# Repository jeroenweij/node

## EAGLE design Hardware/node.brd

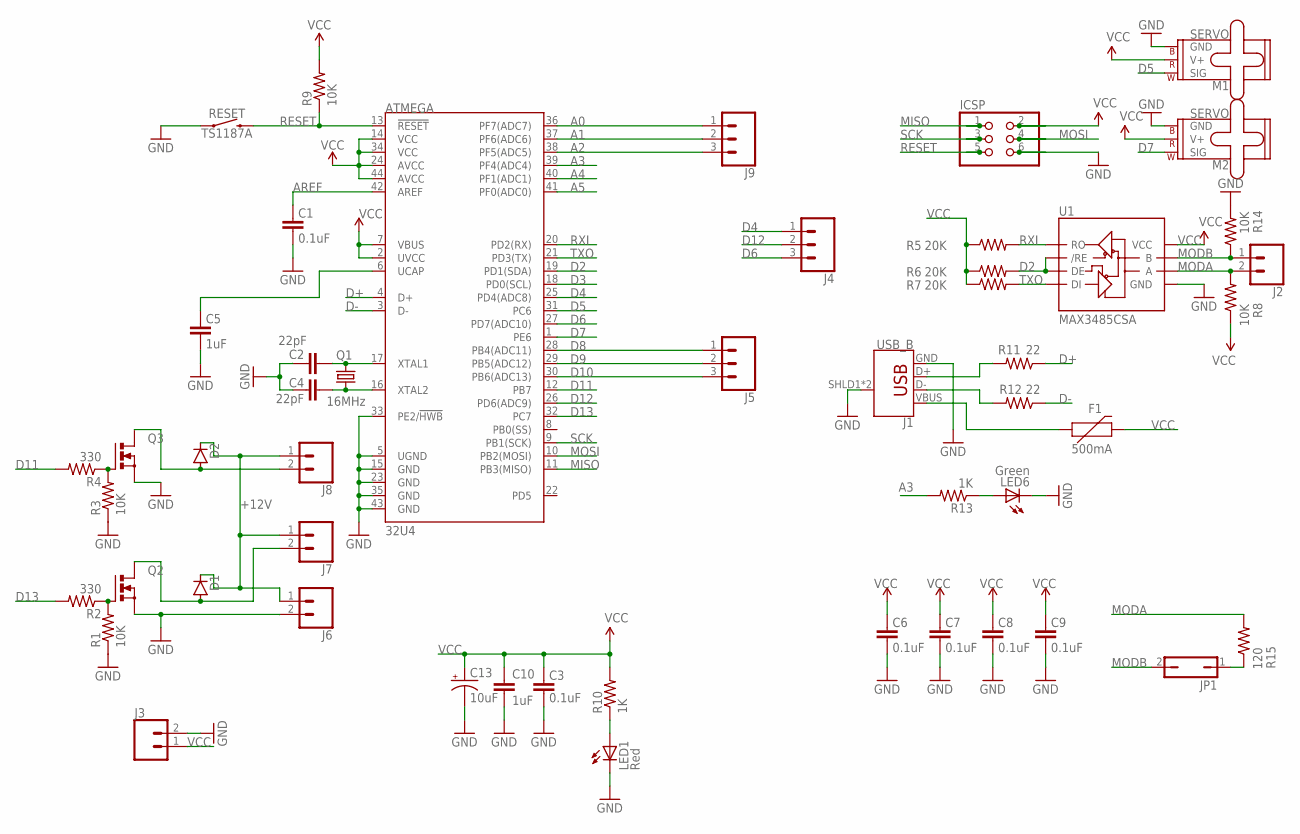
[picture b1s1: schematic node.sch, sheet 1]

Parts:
ATMEGA: 32U4; QFN-44-NOPAD_1:1
C1, C3, C6, C7, C8, C9: 0.1uF; 0603-CAP
C2, C4: 22pF; 0603-CAP
C5, C10: 1uF; 0603-CAP
C13: 10uF; EIA3216
D1, D2: BYS10; SOD106A
F1: 500mA; 1206
ICSP: PINHD-2X3; 2X03
J1: USB_B; USB-B-PTH
J2, J3, J6, J7, J8: CONN_025MM; SCREWTERMINAL-5MM-2
J4, J5, J9: CONN_03-SCREW-5MM; SCREWTERMINAL-5MM-3
JP1: JP1Q; JP1
LED1: Red; LED-0603
LED6: Green; LED-0603
M1, M2: SERVO; 1X03
Q1: 16MHz; 3.2X2.5_KX-7
Q2, Q3: PMOSFET_NTO220BV; TO220BV
R1, R3, R8, R9, R14: 10K; 0603-RES
R2, R4: 330; 0603-RES
R5, R6, R7: 20K; 0603-RES
R10, R13: 1K; 0603-RES
R11, R12: 22; 0603-RES
R15: 120; 0603-RES
RESET: TS1187A; TACTILE_SWITCH_SMD_5.2MM
U1: MAX3485CSA; SO08

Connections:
+12V: D1.K, D2.K, J6.1, J7.1, J8.1
A0: ATMEGA.36 (PF7(ADC7)), J9.1
A1: ATMEGA.37 (PF6(ADC6)), J9.2
A2: ATMEGA.38 (PF5(ADC5)), J9.3
A3: ATMEGA.39 (PF4(ADC4)), R13.2
A4: ATMEGA.40 (PF1(ADC1))
A5: ATMEGA.41 (PF0(ADC0))
AREF: ATMEGA.42 (AREF), C1.2
D2: ATMEGA.19 (PD1(SDA)), R6.2, U1.2 (/RE), U1.3 (DE)
D3: ATMEGA.18 (PD0(SCL))
D4: ATMEGA.25 (PD4(ADC8)), J4.1
D5: ATMEGA.31 (PC6), M1.1 (SIG)
D6: ATMEGA.27 (PD7(ADC10)), J4.3
D7: ATMEGA.1 (PE6), M2.1 (SIG)
D8: ATMEGA.28 (PB4(ADC11)), J5.1
D9: ATMEGA.29 (PB5(ADC12)), J5.2
D10: ATMEGA.30 (PB6(ADC13)), J5.3
D11: ATMEGA.12 (PB7), R4.2
D12: ATMEGA.26 (PD6(ADC9)), J4.2
D13: ATMEGA.32 (PC7), R2.2
D+: ATMEGA.4 (D+), R11.1
D-: ATMEGA.3 (D-), R12.1
GND: ATMEGA.5 (UGND), ATMEGA.15 (GND), ATMEGA.23 (GND), ATMEGA.33 (PE2/!HWB), ATMEGA.35 (GND), ATMEGA.43 (GND), C1.1, C2.2, C3.1, C4.2, C5.1, C6.1, C7.1, C8.1, C9.1, C10.2, C13.C (-), ICSP.6, J1.GND, J1.SHLD1 (SHIELD), J1.SHLD2 (SHIELD), J3.2, J6.2, LED1.C, LED6.C, M1.3 (GND), M2.3 (GND), Q2.S, Q3.S, R1.1, R3.1, R14.2, RESET.1, U1.5 (GND)
MISO: ATMEGA.11 (PB3(MISO)), ICSP.1
MODA: J2.2, R8.2, R15.2, U1.6 (A)
MODB: J2.1, JP1.2, R14.1, U1.7 (B)
MOSI: ATMEGA.10 (PB2(MOSI)), ICSP.4
unnamed: ATMEGA.16 (XTAL2), C4.1, Q1.1
unnamed: ATMEGA.17 (XTAL1), C2.1, Q1.3 (2)
unnamed: JP1.1, R15.1
unnamed: ATMEGA.6 (UCAP), C5.2
unnamed: J1.D-, R12.2
unnamed: Q2.G, R1.2, R2.1
unnamed: J1.D+, R11.2
unnamed: D1.A, J7.2, Q2.D
unnamed: Q3.G, R3.2, R4.1
unnamed: D2.A, J8.2, Q3.D
unnamed: LED6.A, R13.1
unnamed: F1.1, J1.VBUS
unnamed: LED1.A, R10.1
RESET: ATMEGA.13 (!RESET), ICSP.5, R9.1, RESET.3 (2)
RXI: ATMEGA.20 (PD2(RX)), R5.2, U1.1 (RO)
SCK: ATMEGA.9 (PB1(SCK)), ICSP.3
TXO: ATMEGA.21 (PD3(TX)), R7.2, U1.4 (DI)
VCC: ATMEGA.2 (UVCC), ATMEGA.7 (VBUS), ATMEGA.14 (VCC), ATMEGA.24 (AVCC), ATMEGA.34 (VCC), ATMEGA.44 (AVCC), C3.2, C6.2, C7.2, C8.2, C9.2, C10.1, C13.A (+), F1.2, ICSP.2, J3.1, M1.2 (V+), M2.2 (V+), R5.1, R6.1, R7.1, R8.1, R9.2, R10.2, U1.8 (VCC)

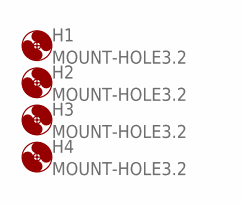
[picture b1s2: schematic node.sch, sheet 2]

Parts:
H1, H2, H3, H4: MOUNT-HOLE3.2; 3,2

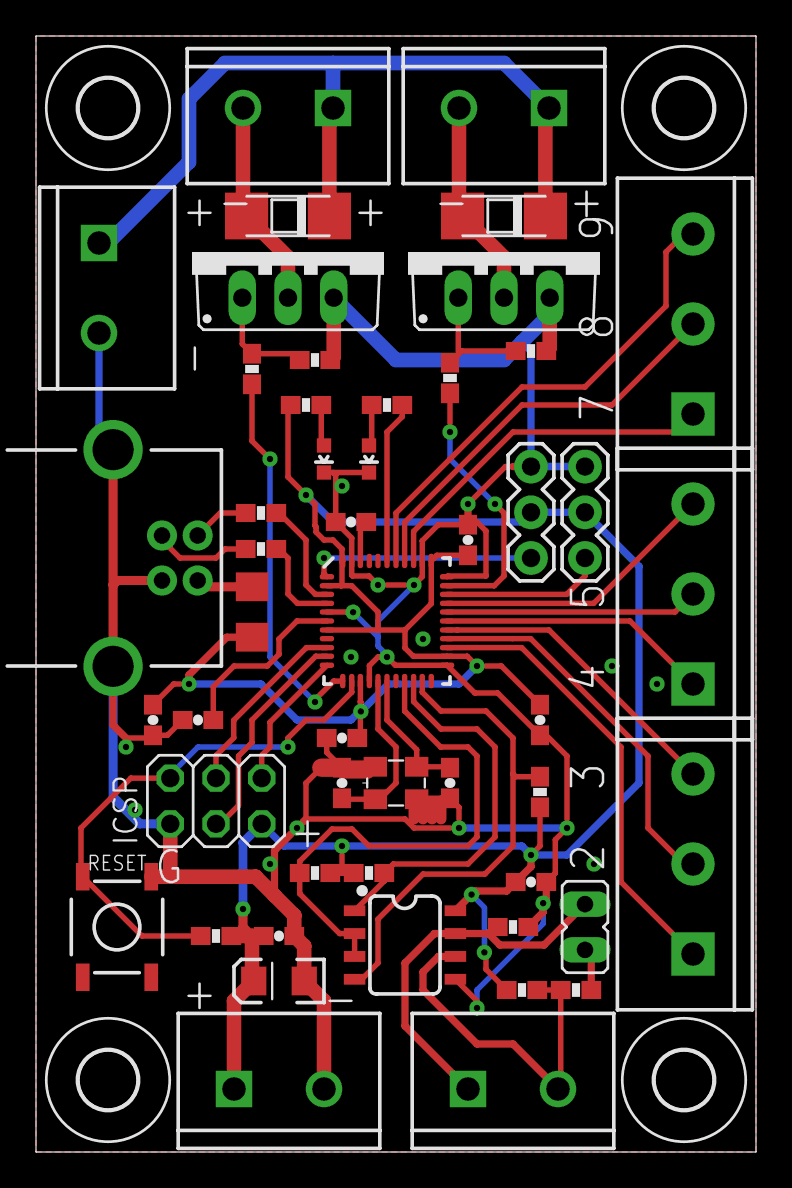
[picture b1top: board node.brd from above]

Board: 2 copper layers, 40.0 x 62.0 mm, 54 parts (0 on the bottom side), 42 nets.

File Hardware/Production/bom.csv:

Comment,Designator,Footprint,LCSC Part #
Diode,D1 D2,SOD106A,C559325
MAX3485CSA,U1,SO08,C2687394
0.1uF,C1 C3 C6 C7 C8 C9,0603-CAP,C14663
1K,R10 R13,0603-RES,C21190
1uF,C5 C10,0603-CAP,C15849
10K,R1 R3 R8 R9 R14,0603-RES,C25804
10uF,C13,EIA3216,C7171
16MHz,Q1,3.2X2.5_KX-7,C13738
20K,R5 R6 R7,0603-RES,C4184
22,R11 R12,0603-RES,C23345
22pF,C2 C4,0603-CAP,C1653
32U4,ATMEGA,QFN-44-NOPAD_1:1,C45874
120,R15,0603-RES,C22787
330,R2 R4,0603-RES,C23138
500mA,F1,1206,C70076
Green,LED6,LED-0603,C72043
Red,LED1,LED-0603,C2286
TS1187A,RESET,TACTILE_SWITCH_SMD_5.2MM,C318884

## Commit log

2021-11-30 Initial hardware schematics
2021-11-30 Schematic v2
2021-11-30 Hardware pcb design
2021-12-01 Finalize hardware design and add production files
2021-12-02 Add tools subrepo
2021-12-02 Bump tools
2021-12-02 Initial software commit
2021-12-03 Setup node communication
2021-12-04 Work on inter Node communication
2021-12-05 Fix bug that master node does not receive channel messages
2021-12-06 Change channel id from int to enum
2021-12-06 Correct pin assignment
2021-12-06 Add debounce to inputs
2021-12-06 Remove extra NodeLib directory
2021-12-06 Cleanup .gitmodules
2021-12-06 Style fixes
2021-12-06 Fix rotation of atmega chip
2021-12-07 Only poll nodes if active nodes where detected
2021-12-07 Update tools
2021-12-08 Fix communication problems
2021-12-10 Update status led handling
2021-12-10 Rename NodeComm to Node
2021-12-13 Move some strings to flash
2021-12-14 Update hardware design
2021-12-15 update style
2021-12-21 Update clang-format
2021-12-21 Communication optimizations
2021-12-22 some bug fixes
2021-12-24 use DelayTimer
2021-12-27 Add hearthbeat
2021-12-29 Fix bug in led pins
2022-01-05 Fix bug in led pin
2022-01-07 Write address to eeprom
2022-01-16 Init channels as not configured
2022-01-17 set baudrate 115200
2022-01-20 Remove possible wait in reading
2022-01-21 reduce node spacing
2022-01-21 add stream operators for message and id
2022-01-23 add script for flashing nodes

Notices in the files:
parts and their libraries:
SparkFun-IC-Microcontroller: Licensing: Creative Commons ShareAlike 4.0 International - https://creativecommons.org/licenses/by-sa/4.0
crystal-geyer_V1_0: Copyright: Geyer-Electronic
